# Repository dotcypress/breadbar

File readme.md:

# BreadBar

Minimal STM32G0 prototyping board.

## PCB

* [Schematics](docs/breadbar.pdf)
* [Gerber files](docs/breadbar_rev_0x01.zip)
* [Order PCB on OSHPark](https://oshpark.com/shared_projects/HnaNiZUA)

## Pinout

## License

Licensed under either of

- Apache License, Version 2.0 ([LICENSE-APACHE](LICENSE-APACHE) or
  http://www.apache.org/licenses/LICENSE-2.0)
- MIT license ([LICENSE-MIT](LICENSE-MIT) or http://opensource.org/licenses/MIT)

at your option.

### Contribution

Unless you explicitly state otherwise, any contribution intentionally submitted
for inclusion in the work by you, as defined in the Apache-2.0 license, shall be
dual licensed as above, without any additional terms or conditions.

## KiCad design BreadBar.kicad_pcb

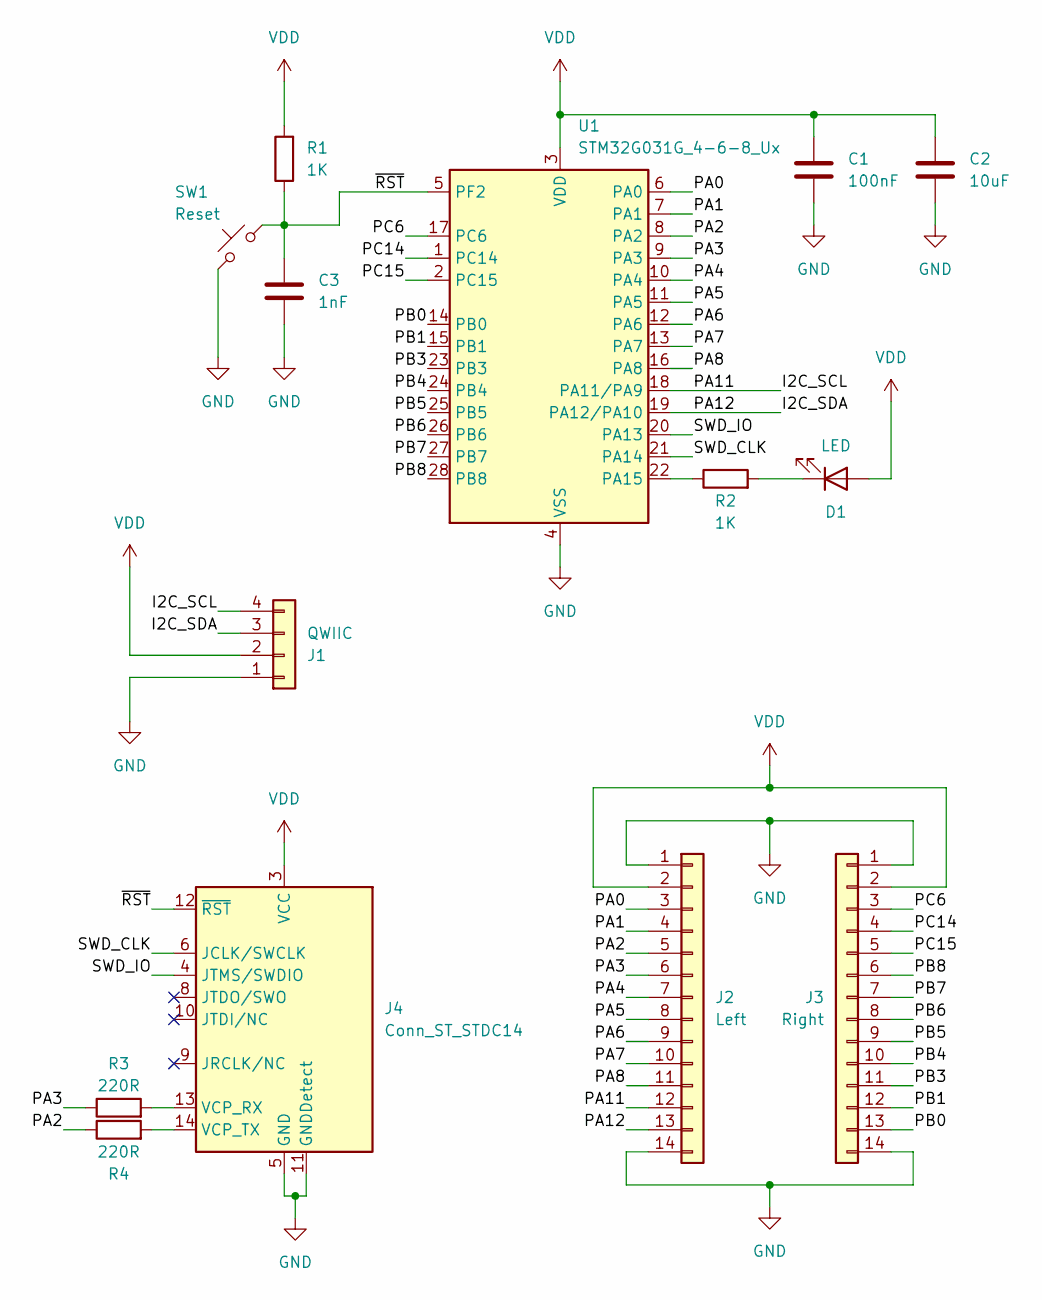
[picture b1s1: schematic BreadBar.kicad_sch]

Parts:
C1: 100nF; C_0603_1608Metric
C2: 10uF; C_0603_1608Metric
C3: 1nF; C_0603_1608Metric
D1: LED; LED_0603_1608Metric
J1: QWIIC; JST_SH_BM04B-SRSS-TB_1x04-1MP_P1.00mm_Vertical
J2: Left; PinHeader_1x14_P2.54mm_Vertical
J3: Right; PinHeader_1x14_P2.54mm_Vertical
J4: Conn_ST_STDC14; PinHeader_2x07_P1.27mm_Vertical_SMD
R1, R2: 1K; R_0603_1608Metric
R3, R4: 220R; R_0603_1608Metric
SW1: Reset; SW_SPST_PTS810
U1: STM32G031G_4-6-8_Ux; QFN-28_4x4mm_P0.5mm

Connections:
/I2C_SCL: J1.4, J2.12, U1.18 (PA11/PA9)
/I2C_SDA: J1.3, J2.13, U1.19 (PA12/PA10)
/PA0: J2.3, U1.6 (PA0)
/PA1: J2.4, U1.7 (PA1)
/PA2: J2.5, R4.1, U1.8 (PA2)
/PA3: J2.6, R3.1, U1.9 (PA3)
/PA4: J2.7, U1.10 (PA4)
/PA5: J2.8, U1.11 (PA5)
/PA6: J2.9, U1.12 (PA6)
/PA7: J2.10, U1.13 (PA7)
/PA8: J2.11, U1.16 (PA8)
/PB0: J3.13, U1.14 (PB0)
/PB1: J3.12, U1.15 (PB1)
/PB3: J3.11, U1.23 (PB3)
/PB4: J3.10, U1.24 (PB4)
/PB5: J3.9, U1.25 (PB5)
/PB6: J3.8, U1.26 (PB6)
/PB7: J3.7, U1.27 (PB7)
/PB8: J3.6, U1.28 (PB8)
/PC6: J3.3, U1.17 (PC6)
/PC14: J3.4, U1.1 (PC14)
/PC15: J3.5, U1.2 (PC15)
/SWD_CLK: J4.6 (JCLK/SWCLK), U1.21 (PA14)
/SWD_IO: J4.4 (JTMS/SWDIO), U1.20 (PA13)
/~RST: C3.1, J4.12 (~RST), R1.1, SW1.2, U1.5 (PF2)
GND: C1.2, C2.2, C3.2, J1.1, J2.1, J2.14, J3.1, J3.14, J4.5 (GND), J4.7 (GND), J4.11 (GNDDetect), SW1.1, U1.4 (VSS)
unnamed: D1.1 (K), R2.2
unnamed: J4.13 (VCP_RX), R3.2
unnamed: J4.14 (VCP_TX), R4.2
unnamed: R2.1, U1.22 (PA15)
VDD: C1.1, C2.1, D1.2 (A), J1.2, J2.2, J3.2, J4.3 (VCC), R1.2, U1.3 (VDD)

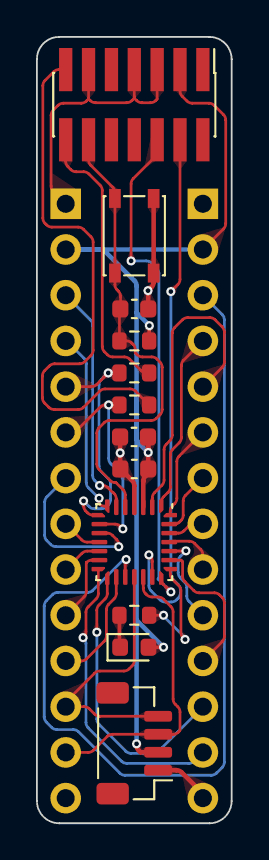
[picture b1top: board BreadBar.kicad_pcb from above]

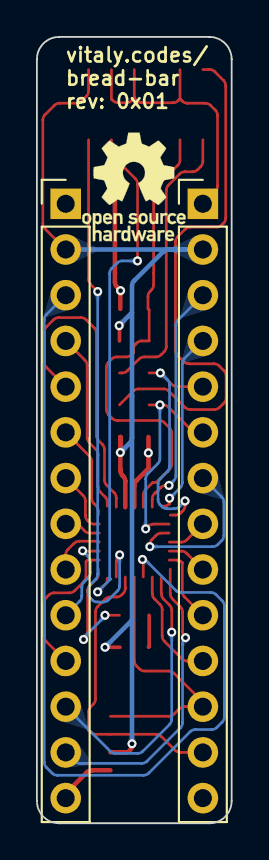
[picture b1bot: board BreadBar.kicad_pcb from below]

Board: 4 copper layers, 10.8 x 43.7 mm, 14 parts (2 on the bottom side), 31 nets.

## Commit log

2023-11-22 rev 0x01
2024-01-10 add BOM
